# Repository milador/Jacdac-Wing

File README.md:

# Jacdaptor-FeatherWing

## Top View: 

## Bottom View:

## Completed:

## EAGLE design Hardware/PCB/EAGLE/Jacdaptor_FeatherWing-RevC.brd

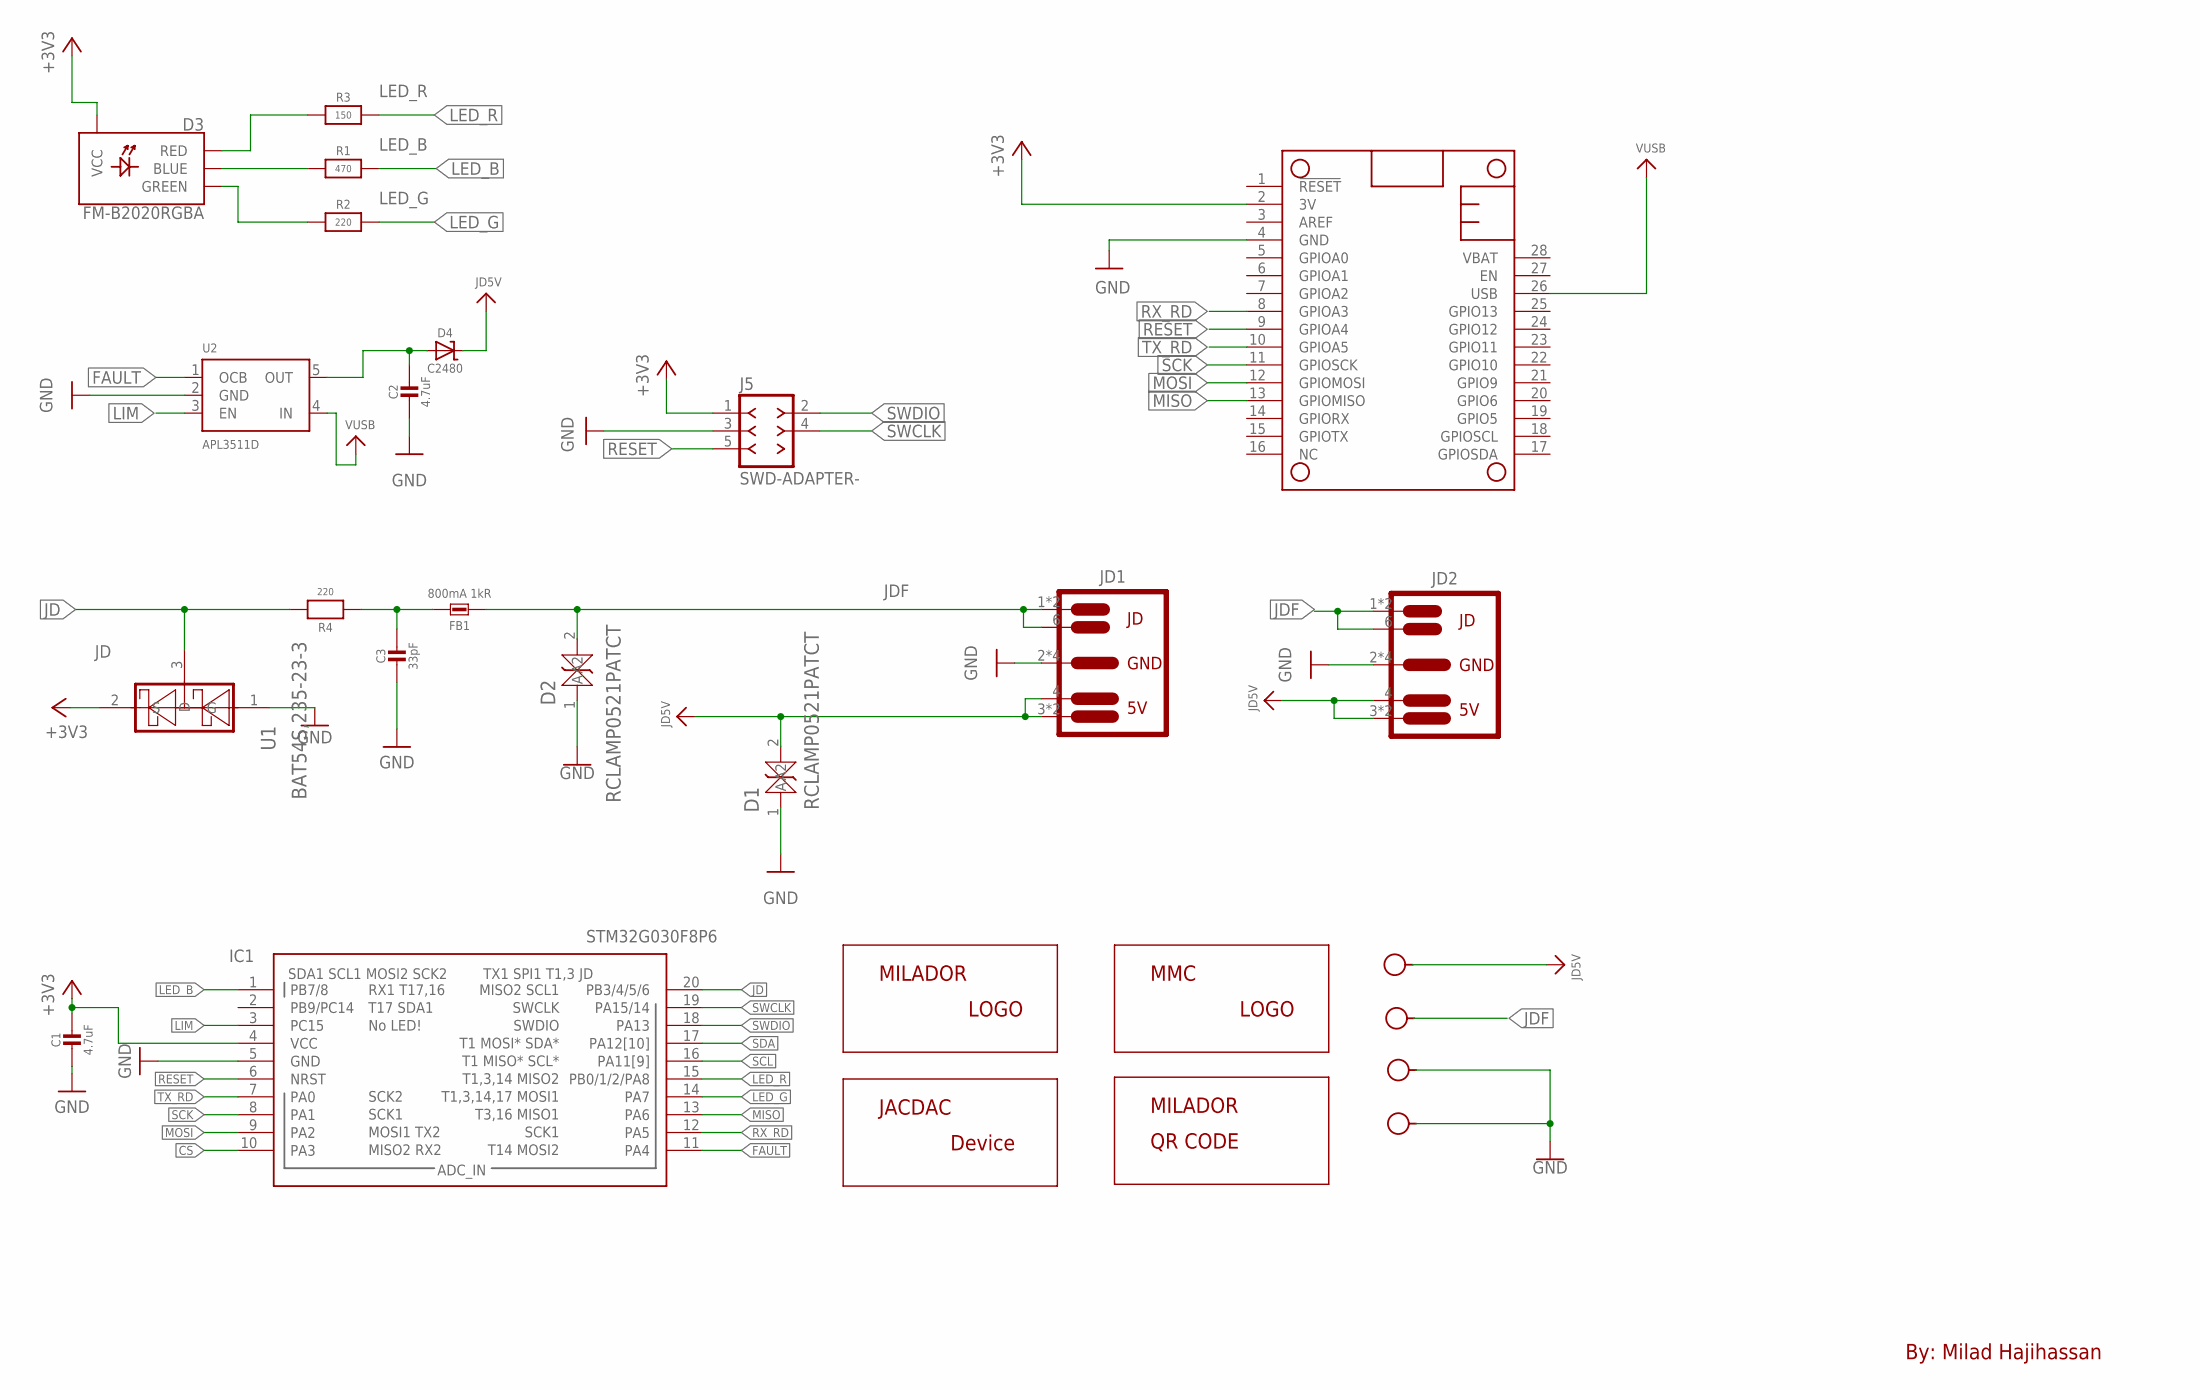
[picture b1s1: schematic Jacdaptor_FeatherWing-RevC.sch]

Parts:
C1, C2: 4.7uF; 0603
C3: 33pF; 0603
D1, D2: RCLAMP0521PATCT; DIODE-ZENER-0402
D3: FM-B2020RGBA; LED-RGB-2121
D4: C2480; DO214AC
FB1: 800mA 1kR; 0603-NO
IC1: STM32G030F8P6; SOP65P640X120-20N
J1: JACDAC-M3-DATA; M3-HOLE-DATA
J2: JACDAC-M3-PWR; M3-HOLE-PWR
J3, J4: JACDAC-M3-GND; M3-HOLE-GND
J5: SWD-ADAPTER-; SWD-ADAPTER
JD1, JD2: JACDAC-EDGE-INNIE; JD-EDGE-INNIE
LABEL_DEVICE: MILADOR-JACDAC-DEVICE-JACDAPTOR-WING; JACDAPTOR-FEATHERWING
LABEL_LOGO: MILADOR-LOGO-SM; MILADOR_LOGO2
LABEL_MMC: MMC_LOGO-XSM; MMC_X-SMALL_LOGO
LABEL_QR_CODE: MILADOR-QR-CODE-JACDAC-FEATHERWING; MILADOR_QR_JACDAC_FEATHERWING
MS1: ADAFRUIT_FEATHERWING_NODIM; ADAFRUIT_FEATHERWING_DIM
R1: 470; 0603
R2, R4: 220; 0603
R3: 150; 0603
U1: BAT54S,235-23-3; SOT23-3
U2: APL3511D; SOT23-5

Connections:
+3V3: C1.1, D3.PLUS (VCC), IC1.4 (VCC), J5.1 (VCC_1), MS1.2 (3V), U1.2 (S)
CS: IC1.10 (PA3)
FAULT: IC1.11 (PA4), U2.1 (OCB)
GND: C1.2, C2.2, C3.2, D1.1 (A), D2.1 (A), IC1.5 (GND), J3.H, J4.H, J5.3 (GND_3), JD1.2 (1), JD1.5 (1), JD1.P$2 (1), JD1.P$4 (1), JD2.2 (1), JD2.5 (1), JD2.P$2 (1), JD2.P$4 (1), MS1.4 (GND), U1.1 (G), U2.2 (GND)
JD: IC1.20 (PB3/4/5/6), R4.2, U1.3 (D)
JD5V: D1.2 (A2), D4.C, J2.H, JD1.3, JD1.4, JD1.P$1 (3), JD2.3, JD2.4, JD2.P$1 (3)
JDF: D2.2 (A2), FB1.2, J1.H, JD1.1 (2), JD1.6, JD1.P$3 (2), JD2.1 (2), JD2.6, JD2.P$3 (2)
LED_B: IC1.1 (PB7/8), R1.2
LED_G: IC1.14 (PA7), R2.2
LED_R: IC1.15 (PB0/1/2/PA8), R3.2
LIM: IC1.3 (PC15), U2.3 (EN)
MISO: IC1.13 (PA6), MS1.13 (GPIOMISO)
MOSI: IC1.9 (PA2), MS1.12 (GPIOMOSI)
unnamed: D3.B- (BLUE), R1.1
unnamed: D3.G- (GREEN), R2.1
unnamed: D3.R- (RED), R3.1
unnamed: C3.1, FB1.1, R4.1
OUT: C2.1, D4.A, U2.5 (OUT)
RESET: IC1.6 (NRST), J5.5 (RESET_5), MS1.9 (GPIOA4)
RX_RD: IC1.12 (PA5), MS1.8 (GPIOA3)
SCK: IC1.8 (PA1), MS1.11 (GPIOSCK)
SCL: IC1.16 (PA11[9])
SDA: IC1.17 (PA12[10])
SWCLK: IC1.19 (PA15/14), J5.4 (SWCLK_4)
SWDIO: IC1.18 (PA13), J5.2 (SWDIO_2)
TX_RD: IC1.7 (PA0), MS1.10 (GPIOA5)
VUSB: MS1.26 (USB), U2.4 (IN)

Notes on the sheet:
By: Milad Hajihassan

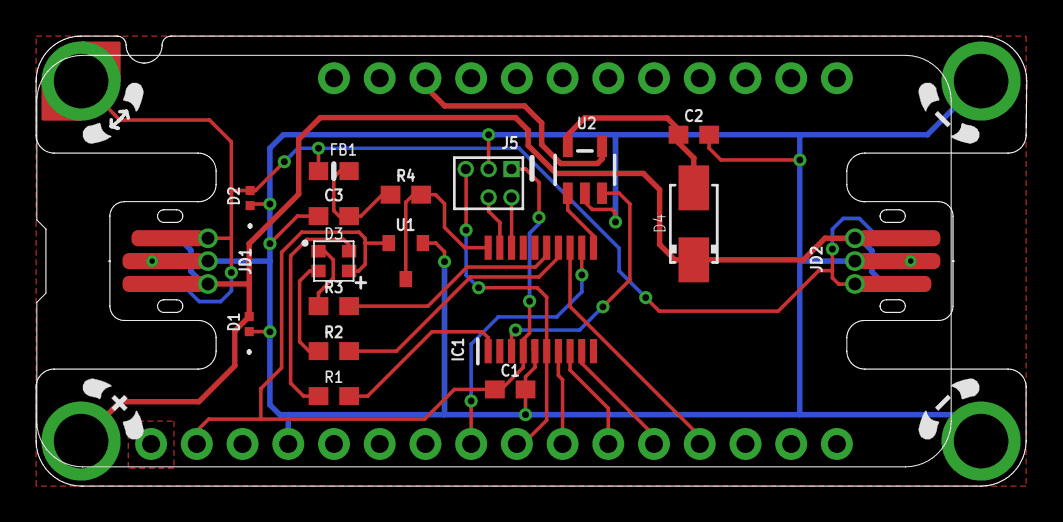
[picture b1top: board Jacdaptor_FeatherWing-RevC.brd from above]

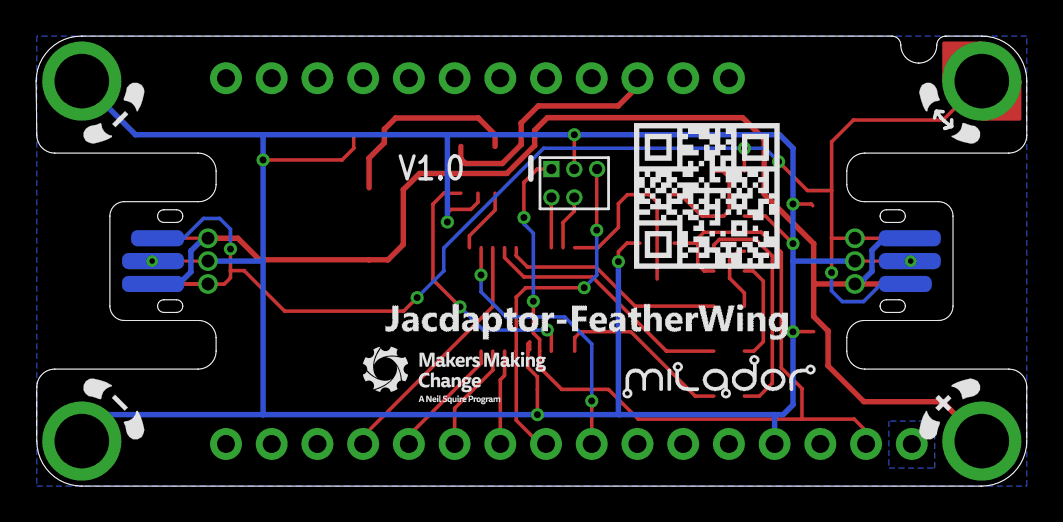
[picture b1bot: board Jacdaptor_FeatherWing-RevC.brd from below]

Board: 2 copper layers, 55.0 x 25.0 mm, 27 parts (4 on the bottom side), 24 nets.

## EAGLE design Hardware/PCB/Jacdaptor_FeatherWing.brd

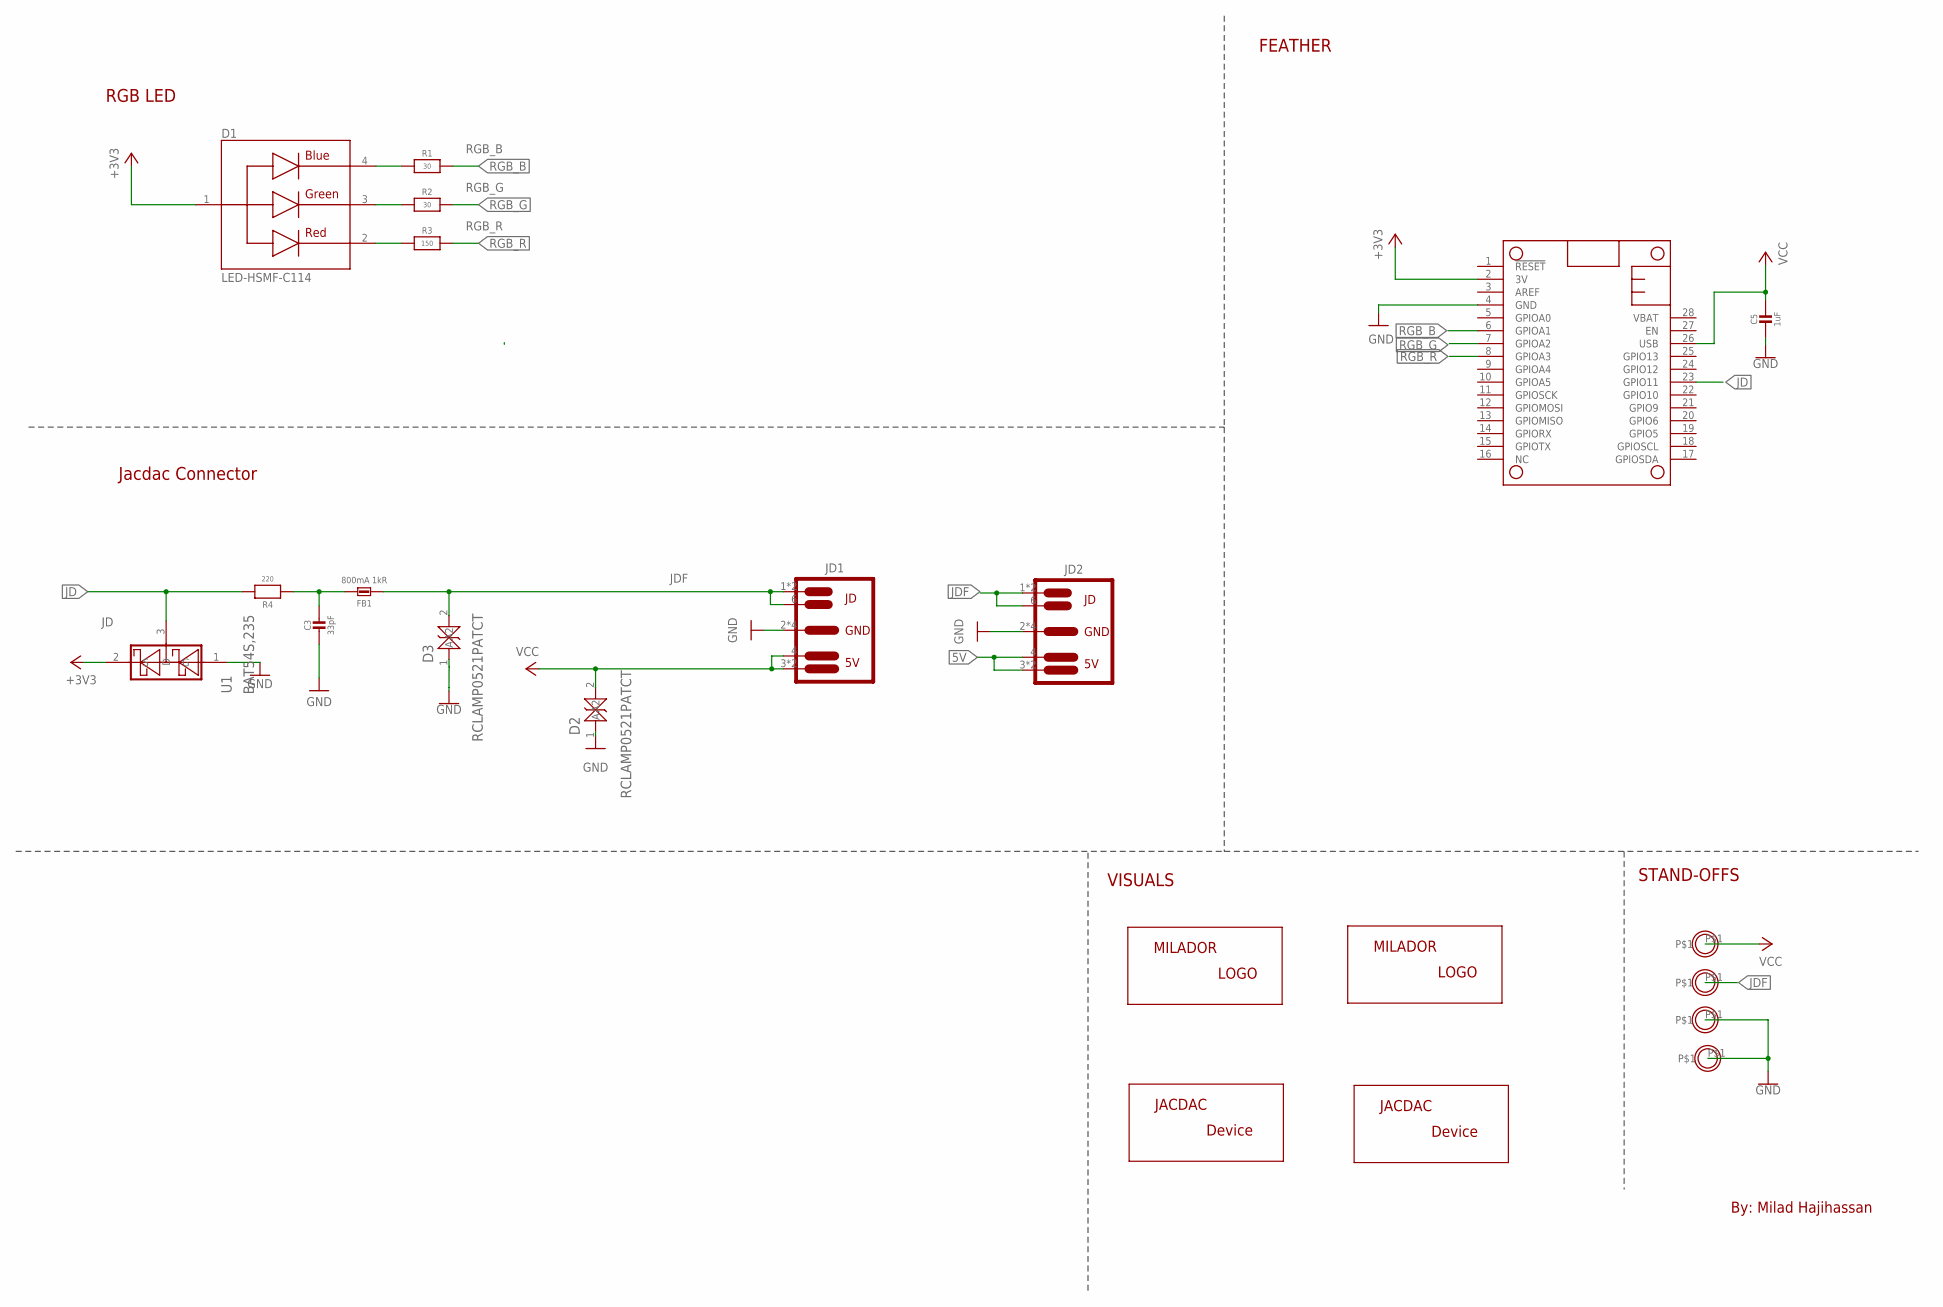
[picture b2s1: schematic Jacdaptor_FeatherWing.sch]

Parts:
C3: 33pF; 0603
C5: 1uF; 0603
D1: LED-HSMF-C114; DIOSC160X150X35-4N
D2, D3: RCLAMP0521PATCT; DIODE-ZENER-0402
FB1: 800mA 1kR; 0603-NO
H1, H2, H3, H4: MOUNTINGHOLE2.5; MOUNTINGHOLE_2.5_PLATED
JD1, JD2: JACDAC-EDGE-INNIE; JD-EDGE-INNIE
LABEL_DEVICE_BOTTOM: MILADOR-JACDAC-DEVICE-JACDAPTOR-WING; JACDAPTOR-FEATHERWING
LABEL_DEVICE_TOP: MILADOR-JACDAC-DEVICE-JACDAPTOR-WING-SM; JACDAPTOR-FEATHERWING-SM
LABEL_LOGO_BOTTOM: MILADOR-LOGO-SM; MILADOR_LOGO2
LABEL_LOGO_TOP: MILADOR-LOGO-SM; MILADOR_LOGO2
MS1: ADAFRUIT_FEATHERWING_NODIM; ADAFRUIT_FEATHERWING_DIM
R1, R2: 30; 0603
R3: 150; 0603
R4: 220; 0603
U1: BAT54S,235; SOT23-3

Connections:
5V: C5.1, D2.2 (A2), H1.P$1, JD1.3, JD1.4, JD1.P$1 (3), JD2.3, JD2.4, JD2.P$1 (3), MS1.26 (USB)
+3V3: D1.1, MS1.2 (3V), U1.2 (S)
GND: C3.2, C5.2, D2.1 (A), D3.1 (A), H3.P$1, H4.P$1, JD1.2 (1), JD1.5 (1), JD1.P$2 (1), JD1.P$4 (1), JD2.2 (1), JD2.5 (1), JD2.P$2 (1), JD2.P$4 (1), MS1.4 (GND), U1.1 (G)
JD: MS1.23 (GPIO11), R4.2, U1.3 (D)
JDF: D3.2 (A2), FB1.2, H2.P$1, JD1.1 (2), JD1.6, JD1.P$3 (2), JD2.1 (2), JD2.6, JD2.P$3 (2)
unnamed: D1.4, R1.1
unnamed: D1.3, R2.1
unnamed: D1.2, R3.1
unnamed: C3.1, FB1.1, R4.1
RGB_B: MS1.6 (GPIOA1), R1.2
RGB_G: MS1.7 (GPIOA2), R2.2
RGB_R: MS1.8 (GPIOA3), R3.2

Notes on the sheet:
By: Milad Hajihassan
STAND-OFFS
VISUALS
RGB LED
Jacdac Connector
FEATHER

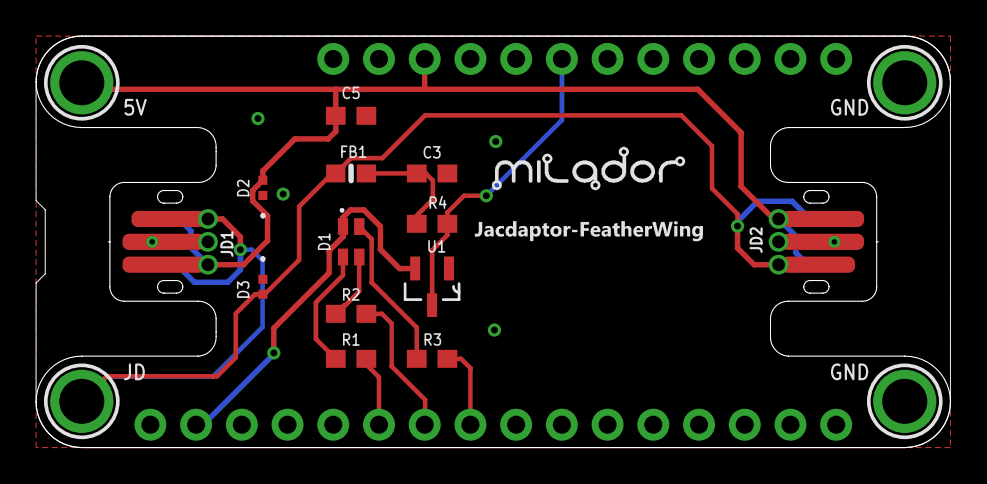
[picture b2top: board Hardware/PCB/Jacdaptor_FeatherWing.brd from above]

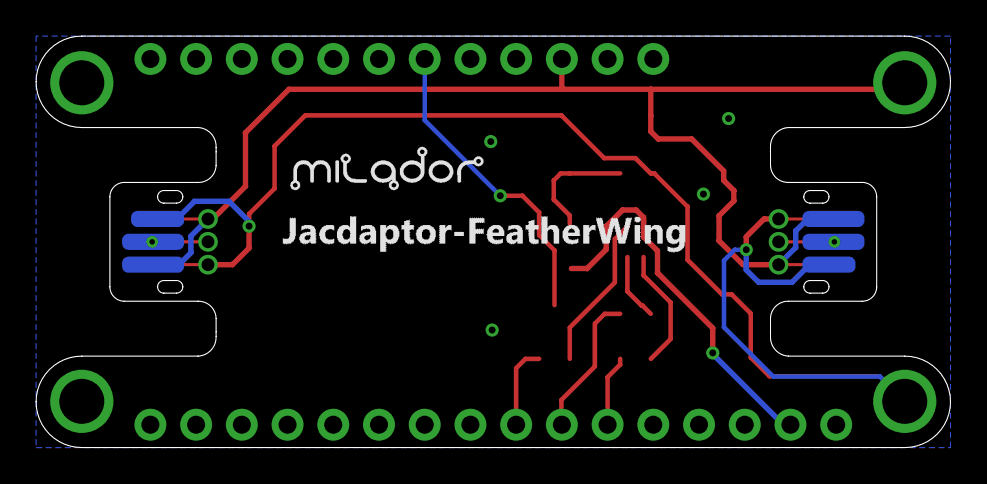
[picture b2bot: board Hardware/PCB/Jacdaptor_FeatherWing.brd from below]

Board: 2 copper layers, 50.8 x 22.9 mm, 22 parts (2 on the bottom side), 12 nets.

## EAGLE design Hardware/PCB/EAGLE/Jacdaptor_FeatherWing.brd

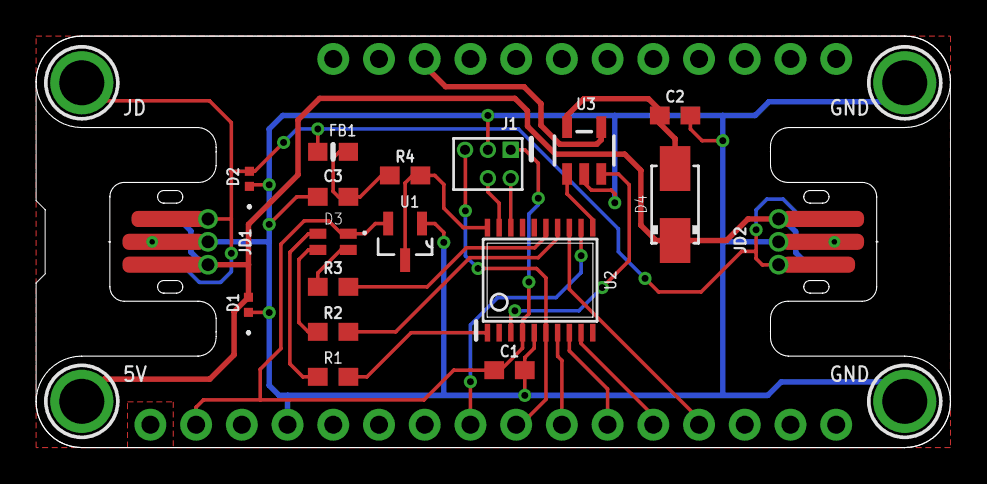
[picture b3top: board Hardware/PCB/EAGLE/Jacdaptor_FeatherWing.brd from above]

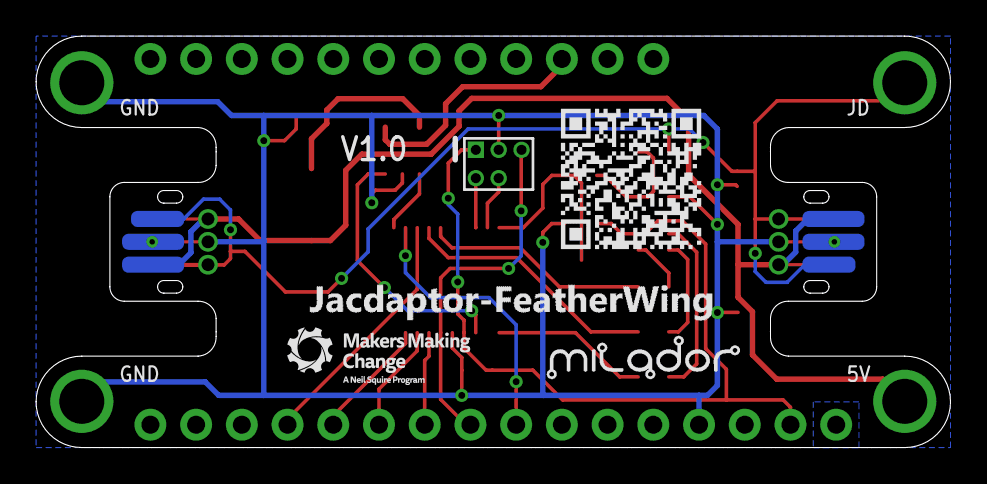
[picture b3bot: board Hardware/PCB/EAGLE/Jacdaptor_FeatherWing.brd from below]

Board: 2 copper layers, 50.8 x 22.9 mm, 27 parts (4 on the bottom side), 24 nets.

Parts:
C1, C2: 4.7uF; 0603
C3: 33pF; 0603
D1, D2: DIODE-ZENER-AA-RCLAMP0521PATCT; DIODE-ZENER-0402
D3: LED-HSMF-C114; DIOSC160X150X35-4N
D4: C2480; DO214AC
FB1: 800mA 1kR; 0603-NO
H1, H2, H3, H4: MOUNTINGHOLE2.5; MOUNTINGHOLE_2.5_PLATED
J1: SWD-ADAPTER-; SWD-ADAPTER
JD1, JD2: JACDAC-EDGE-INNIE; JD-EDGE-INNIE
LABEL_DEVICE: MILADOR-JACDAC-DEVICE-JACDAPTOR-WING; JACDAPTOR-FEATHERWING
LABEL_LOGO: MILADOR-LOGO-SM; MILADOR_LOGO2
LABEL_MMC: MMC_LOGO-XSM; MMC_X-SMALL_LOGO
LABEL_QR_CODE: MILADOR-QR-CODE-JACDAC-FEATHERWING; MILADOR_QR_JACDAC_FEATHERWING
MS1: ADAFRUIT_FEATHERWING_NODIM; ADAFRUIT_FEATHERWING_DIM
R1, R2: 30; 0603
R3: 150; 0603
R4: 220; 0603
U1: BAT54S,235; SOT23-3
U2: STM32G030F6P6; TSSOP20
U3: APL3511D; SOT23-5

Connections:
+3V3: C1.1, D3.1, J1.1, MS1.2, U1.2, U2.4
FAULT: U2.11, U3.1
GND: C1.2, C2.2, C3.2, D1.1, D2.1, H3.P$1, H4.P$1, J1.3, JD1.2, JD1.5, JD1.P$2, JD1.P$4, JD2.2, JD2.5, JD2.P$2, JD2.P$4, MS1.4, U1.1, U2.5, U3.2
JD: R4.2, U1.3, U2.20
JD5V: D1.2, D4.C, H1.P$1, JD1.3, JD1.4, JD1.P$1, JD2.3, JD2.4, JD2.P$1
JDF: D2.2, FB1.2, H2.P$1, JD1.1, JD1.6, JD1.P$3, JD2.1, JD2.6, JD2.P$3
LED_B: R1.2, U2.1
LED_G: R2.2, U2.14
LED_R: R3.2, U2.15
LIM: U2.3, U3.3
MISO: MS1.13, U2.13
MOSI: MS1.12, U2.9
unnamed: D3.4, R1.1
unnamed: D3.3, R2.1
unnamed: D3.2, R3.1
unnamed: C3.1, FB1.1, R4.1
OUT: C2.1, D4.A, U3.5
RESET: J1.5, MS1.9, U2.6
RX_RD: MS1.8, U2.12
SCK: MS1.11, U2.8
SWCLK: J1.4, U2.19
SWDIO: J1.2, U2.18
TX_RD: MS1.10, U2.7
VUSB: MS1.26, U3.4

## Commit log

2022-06-24 Added EAGLE Design files
2022-07-07 Updated design
2022-07-09 Updated RevB
2022-07-14 Updated design RevB
2022-07-14 Updated images
2022-07-14 Removed images
2022-07-14 Added images
2022-07-16 Added RevC
2022-08-08 Updated pdf

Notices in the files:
parts and their libraries:
COPYRIGHT: Copyright (C) 2021 Ultra Librarian. All rights reserved.
SparkFun-PowerSymbols: Licensing: Creative Commons ShareAlike 4.0 International - https://creativecommons.org/licenses/by-sa/4.0
